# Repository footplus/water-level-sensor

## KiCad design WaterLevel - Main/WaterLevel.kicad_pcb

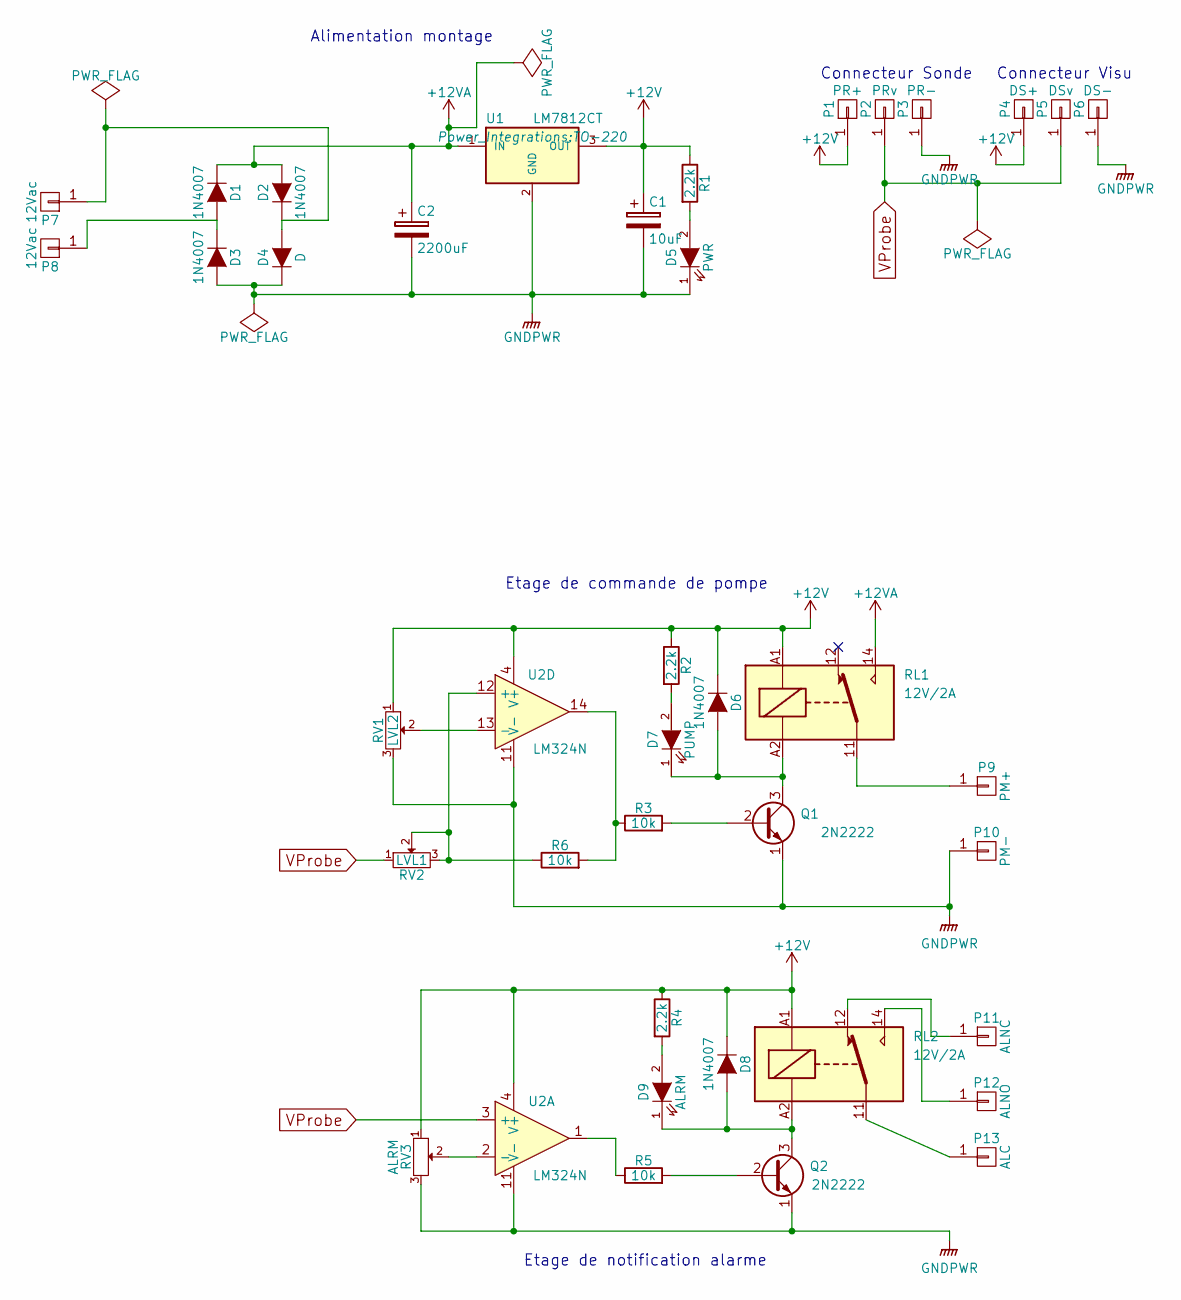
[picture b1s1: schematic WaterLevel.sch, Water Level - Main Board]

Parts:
C1: 10uF; C_Radial_D5_L11_P2.5
C2: 2200uF; C_Radial_D14_L25_P5
D1, D2, D3, D6, D8: 1N4007; Diode_DO-41_SOD81_Horizontal_RM10
D4: D; Diode_DO-41_SOD81_Horizontal_RM10
D5: PWR; LED-5MM
D7: PUMP; LED-5MM
D9: ALRM; LED-5MM
P1: PR+; Big_Square_Pad_3mm_1mmDrill
P2: PRv; Big_Square_Pad_3mm_1mmDrill
P3: PR-; Big_Square_Pad_3mm_1mmDrill
P4: DS+; Big_Square_Pad_3mm_1mmDrill
P5: DSv; Big_Square_Pad_3mm_1mmDrill
P6: DS-; Big_Square_Pad_3mm_1mmDrill
P7, P8: 12Vac; Big_Square_Pad_3mm_1mmDrill
P9: PM+; Big_Square_Pad_3mm_1mmDrill
P10: PM-; Big_Square_Pad_3mm_1mmDrill
P11: ALNC; Big_Square_Pad_3mm_1mmDrill
P12: ALNO; Big_Square_Pad_3mm_1mmDrill
P13: ALC; Big_Square_Pad_3mm_1mmDrill
Q1, Q2: 2N2222; TO-18_3Pin
R1, R2, R4: 2.2k; Resistor_Horizontal_RM7mm
R3, R5, R6: 10k; Resistor_Horizontal_RM7mm
RL1, RL2: 12V/2A; Relay_1RT_Hongfa_HF33F
RV1: LVL2; Potentiometer_Trimmer-Piher_PT10-V10_horizontal
RV2: LVL1; Potentiometer_Trimmer-Piher_PT10-V10_horizontal
RV3: ALRM; Potentiometer_Trimmer-Piher_PT10-V10_horizontal
U1: LM7812CT; TO-220
U2: LM324N; DIP-14_W7.62mm_LongPads

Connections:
+12V: C1.1, D6.1 (K), D8.1 (K), P1.1, P4.1, R1.1, R2.1, R4.1, RL1.A1, RL2.A1, RV1.1, RV3.1, U1.3 (OUT), U2.4 (V+)
+12VA: C2.1, D1.1 (K), D2.2 (A), RL1.14, U1.1 (IN)
GNDPWR: C1.2, C2.2, D3.2 (A), D4.1 (K), D5.1 (K), P3.1, P6.1, P10.1, Q1.1 (E), Q2.1 (E), RV1.3, RV3.3, U1.2 (GND), U2.11 (V-)
unnamed: D1.2 (A), D3.1 (K), P8.1
unnamed: D2.1 (K), D4.2 (A), P7.1
unnamed: D5.2 (A), R1.2
unnamed: D6.2 (A), D7.1 (K), Q1.3 (C), RL1.A2
unnamed: D7.2 (A), R2.2
unnamed: D8.2 (A), D9.1 (K), Q2.3 (C), RL2.A2
unnamed: D9.2 (A), R4.2
unnamed: P9.1, RL1.11
unnamed: P11.1, RL2.12
unnamed: P12.1, RL2.14
unnamed: P13.1, RL2.11
unnamed: Q1.2 (B), R3.2
unnamed: Q2.2 (B), R5.2
unnamed: R3.1, R6.2, U2.14
unnamed: R5.1, U2.1
unnamed: R6.1, RV2.2, RV2.3, U2.12 (+)
unnamed: RV1.2, U2.13 (-)
unnamed: RV3.2, U2.2 (-)
VProbe: P2.1, P5.1, RV2.1, U2.3 (+)

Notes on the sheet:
Alimentation montage
Etage de commande de pompe
Connecteur Sonde
Etage de notification alarme
Connecteur Visu

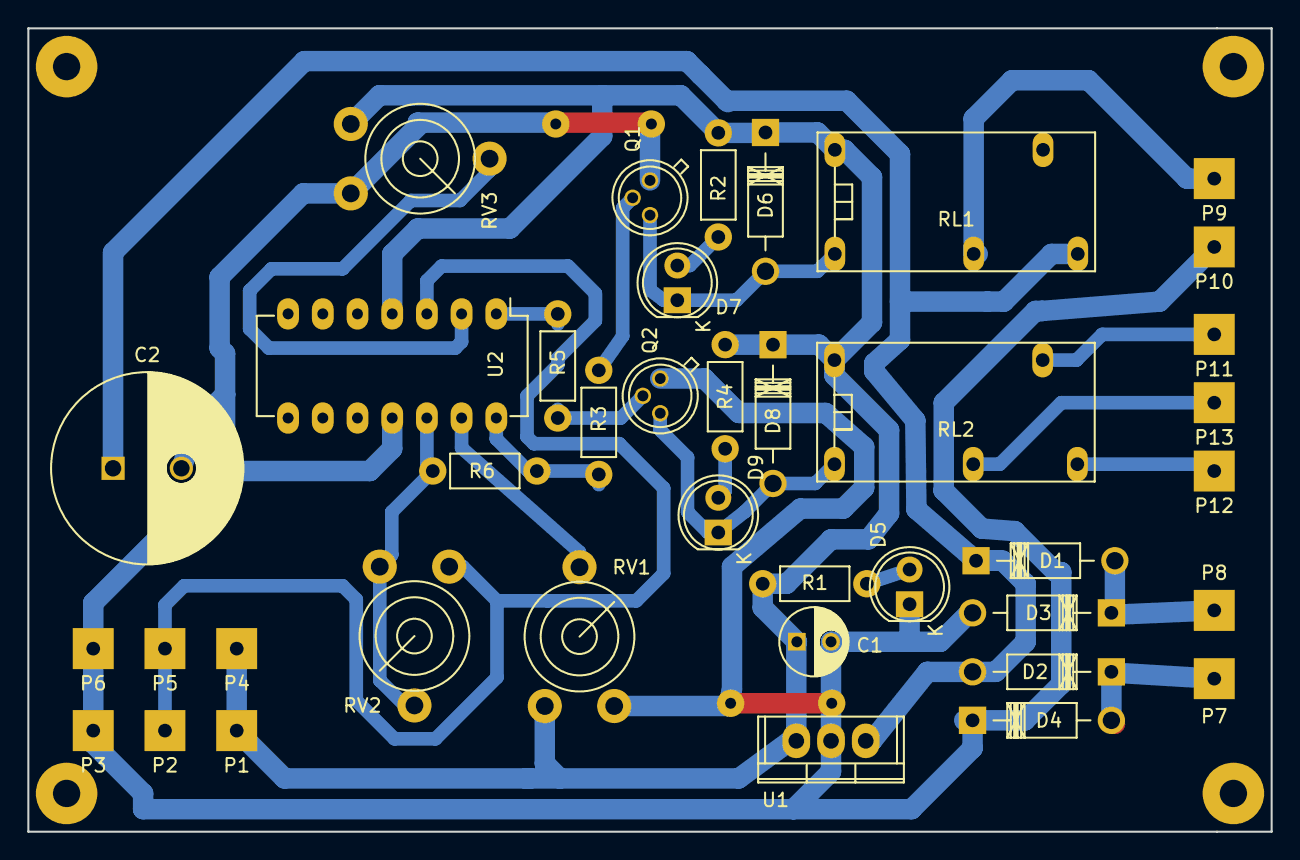
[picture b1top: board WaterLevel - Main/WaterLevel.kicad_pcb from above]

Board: 2 copper layers, 91.0 x 58.8 mm, 39 parts (0 on the bottom side), 22 nets.

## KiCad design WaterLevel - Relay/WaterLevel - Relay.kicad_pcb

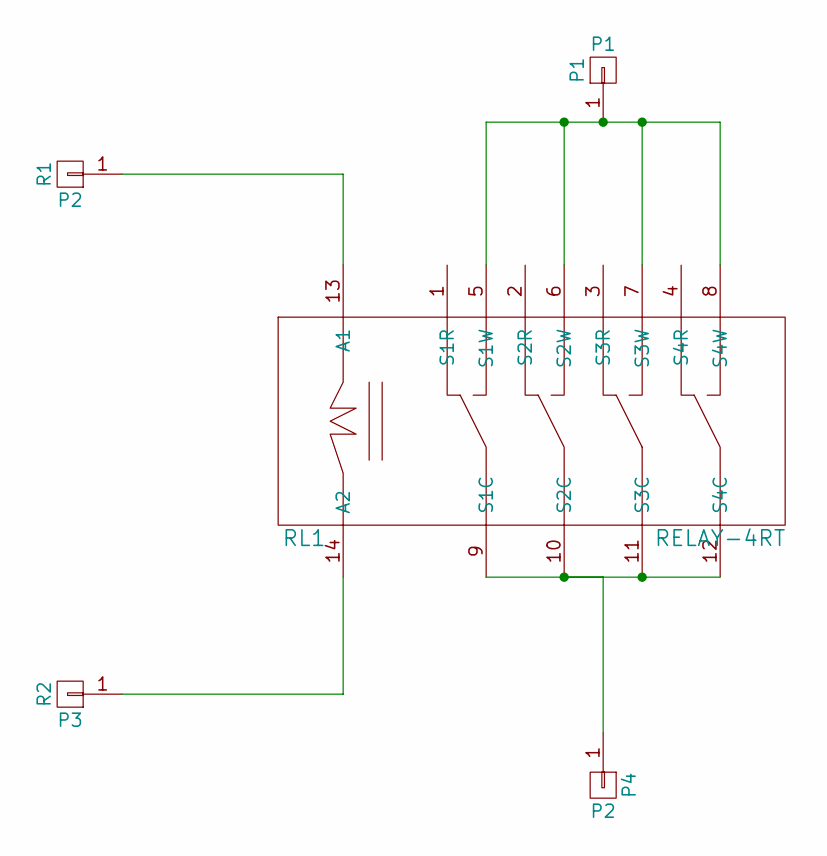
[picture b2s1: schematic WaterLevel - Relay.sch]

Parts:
P1: P1; SolderWirePad_single_2mmDrill
P2: R1; SolderWirePad_single_2mmDrill
P3: R2; SolderWirePad_single_2mmDrill
P4: P2; SolderWirePad_single_2mmDrill
RL1: RELAY-4RT; Relay_4RT_Hongfa_HF18FF

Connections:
unnamed: P1.1, RL1.5 (S1W), RL1.6 (S2W), RL1.7 (S3W), RL1.8 (S4W)
unnamed: P2.1, RL1.13 (A1)
unnamed: P3.1, RL1.14 (A2)
unnamed: P4.1, RL1.9 (S1C), RL1.10 (S2C), RL1.11 (S3C), RL1.12 (S4C)

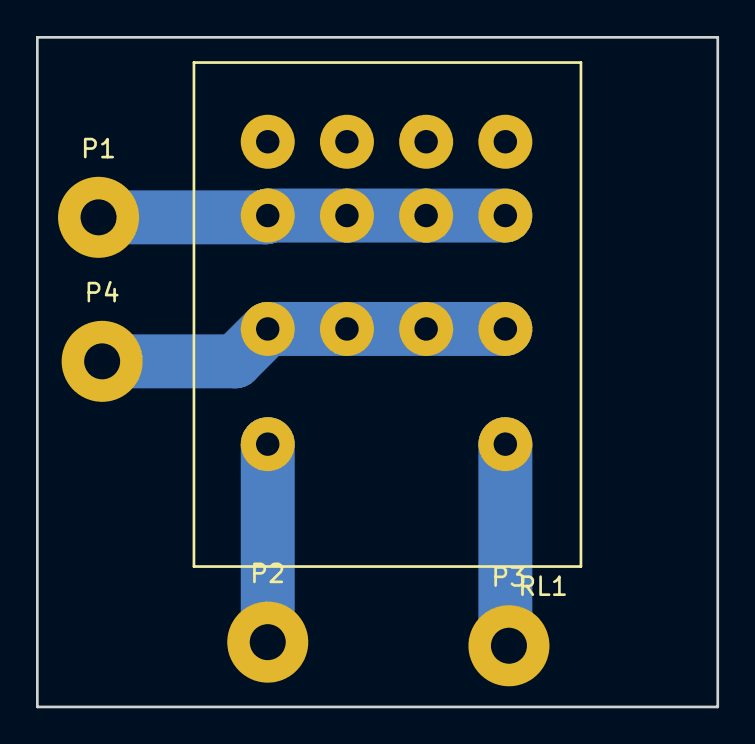
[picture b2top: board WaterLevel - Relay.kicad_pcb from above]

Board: 2 copper layers, 37.8 x 37.2 mm, 5 parts (0 on the bottom side), 4 nets.

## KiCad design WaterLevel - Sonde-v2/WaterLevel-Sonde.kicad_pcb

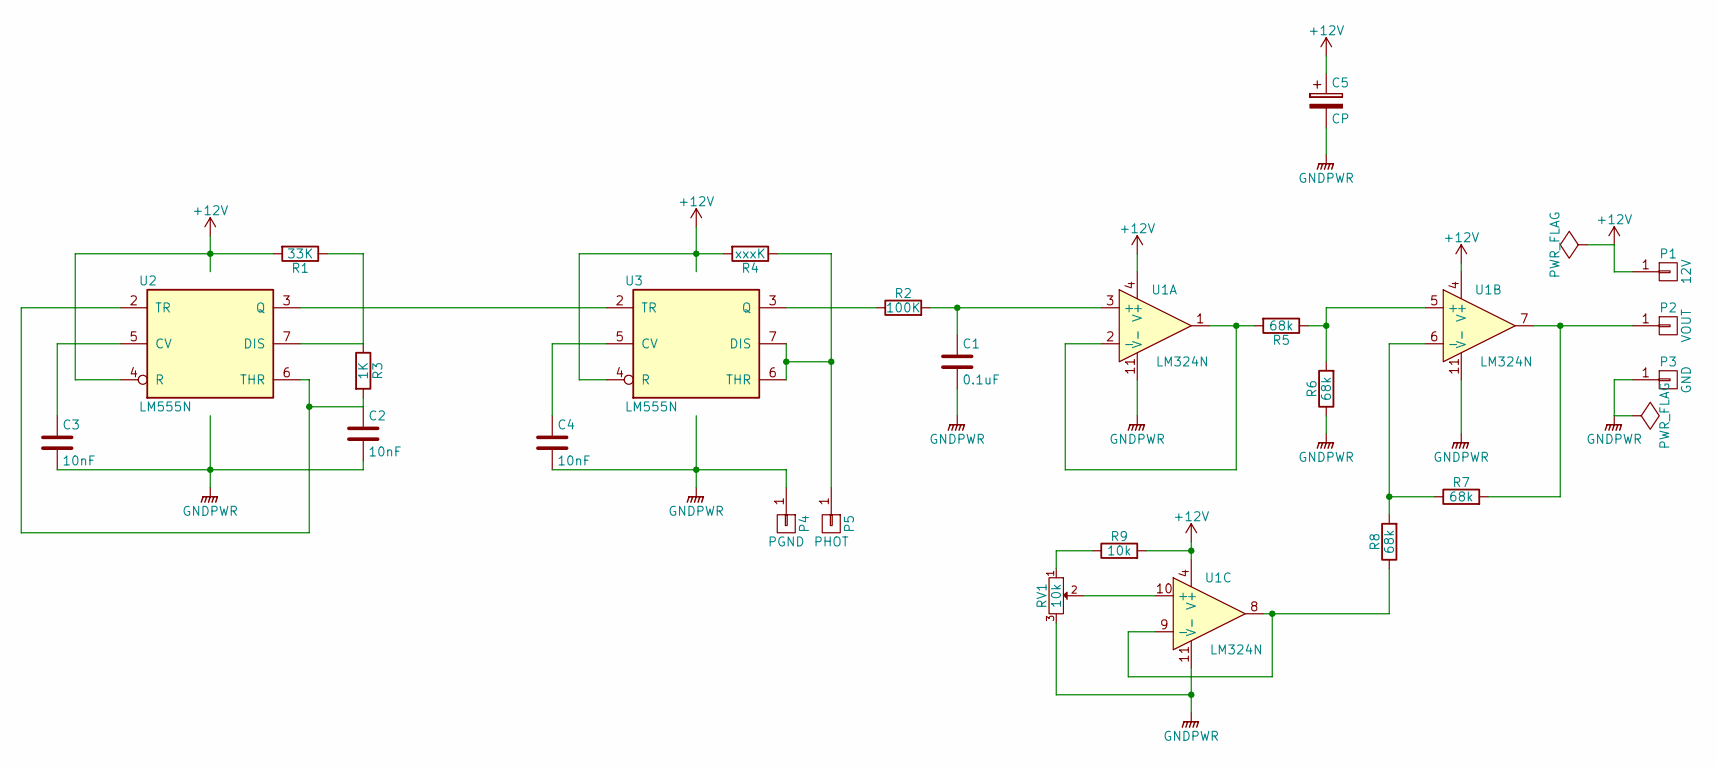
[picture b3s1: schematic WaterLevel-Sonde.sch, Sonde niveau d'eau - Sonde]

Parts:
C1: 0.1uF; C_Rect_L4_W2.5_P2.5
C2, C3: 10nF; C_Rect_L4_W2.5_P2.5
C4: 10nF; C_Rect_L7_W2.5_P5
C5: CP; C_Radial_D5_L11_P2.5
P1: 12V; Big_Square_Pad_3mm_1mmDrill
P2: VOUT; Big_Square_Pad_3mm_1mmDrill
P3: GND; Big_Square_Pad_3mm_1mmDrill
P4: PGND; Big_Square_Pad_3mm_1mmDrill
P5: PHOT; Big_Square_Pad_3mm_1mmDrill
R1: 33K; Resistor_Horizontal_RM7mm
R2: 100K; Resistor_Horizontal_RM7mm
R3: 1K; Resistor_Horizontal_RM7mm
R4: xxxK; Resistor_Horizontal_RM7mm
R5, R6, R7, R8: 68k; Resistor_Horizontal_RM7mm
R9: 10k; Resistor_Horizontal_RM7mm
RV1: 10k; Potentiometer_Spectrol-Type43
U1: LM324N; DIP-14_W7.62mm_LongPads
U2, U3: LM555N; DIP-8_W7.62mm_LongPads

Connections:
+12V: C5.1, P1.1, R1.2, R4.2, R9.2, U1.4 (V+), U2.4 (R), U2.8 (VCC), U3.4 (R), U3.8 (VCC)
GND: C1.2, C2.2, C3.2, C4.2, C5.2, P3.1, P4.1, R6.1, RV1.3, U1.11 (V-), U2.1 (GND), U3.1 (GND)
unnamed: C1.1, R2.2, U1.3 (+)
unnamed: C2.1, R3.2, U2.2 (TR), U2.6 (THR)
unnamed: C3.1, U2.5 (CV)
unnamed: C4.1, U3.5 (CV)
unnamed: P2.1, R7.2, U1.7
unnamed: P5.1, R4.1, U3.6 (THR), U3.7 (DIS)
unnamed: R1.1, R3.1, U2.7 (DIS)
unnamed: R2.1, U3.3 (Q)
unnamed: R5.1, R6.2, U1.5 (+)
unnamed: R5.2, U1.1, U1.2 (-)
unnamed: R7.1, R8.2, U1.6 (-)
unnamed: R8.1, U1.8, U1.9 (-)
unnamed: R9.1, RV1.1
unnamed: RV1.2, U1.10 (+)
unnamed: U2.3 (Q), U3.2 (TR)

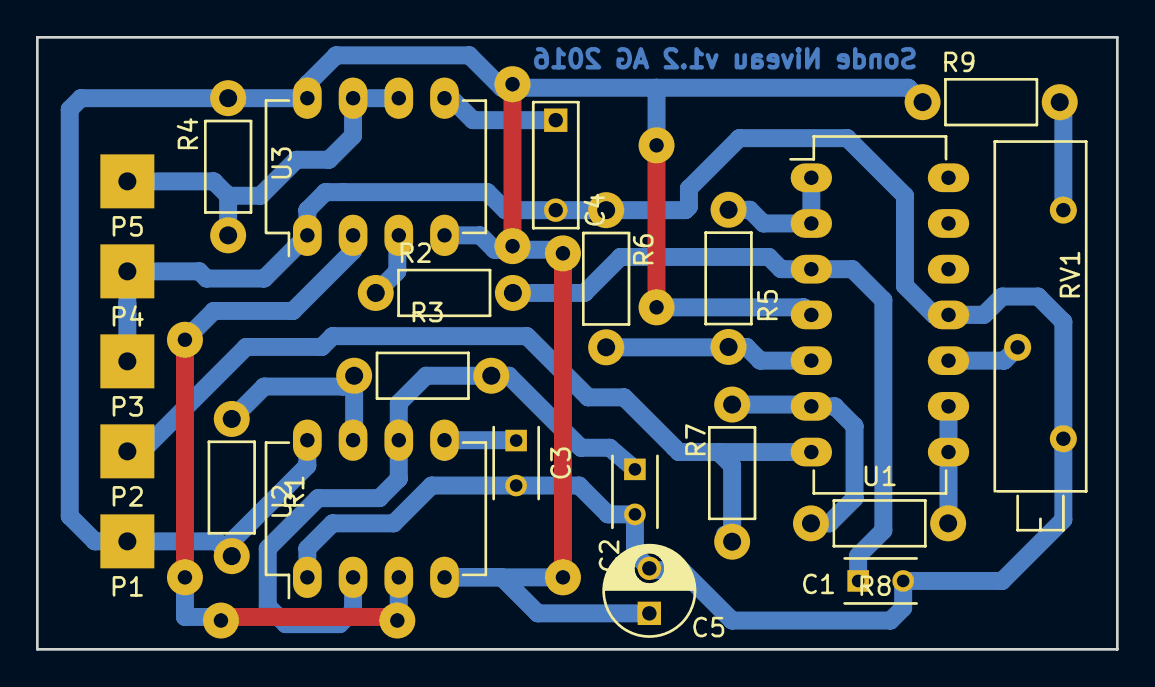
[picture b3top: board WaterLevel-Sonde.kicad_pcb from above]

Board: 2 copper layers, 60.0 x 34.0 mm, 23 parts (0 on the bottom side), 17 nets.

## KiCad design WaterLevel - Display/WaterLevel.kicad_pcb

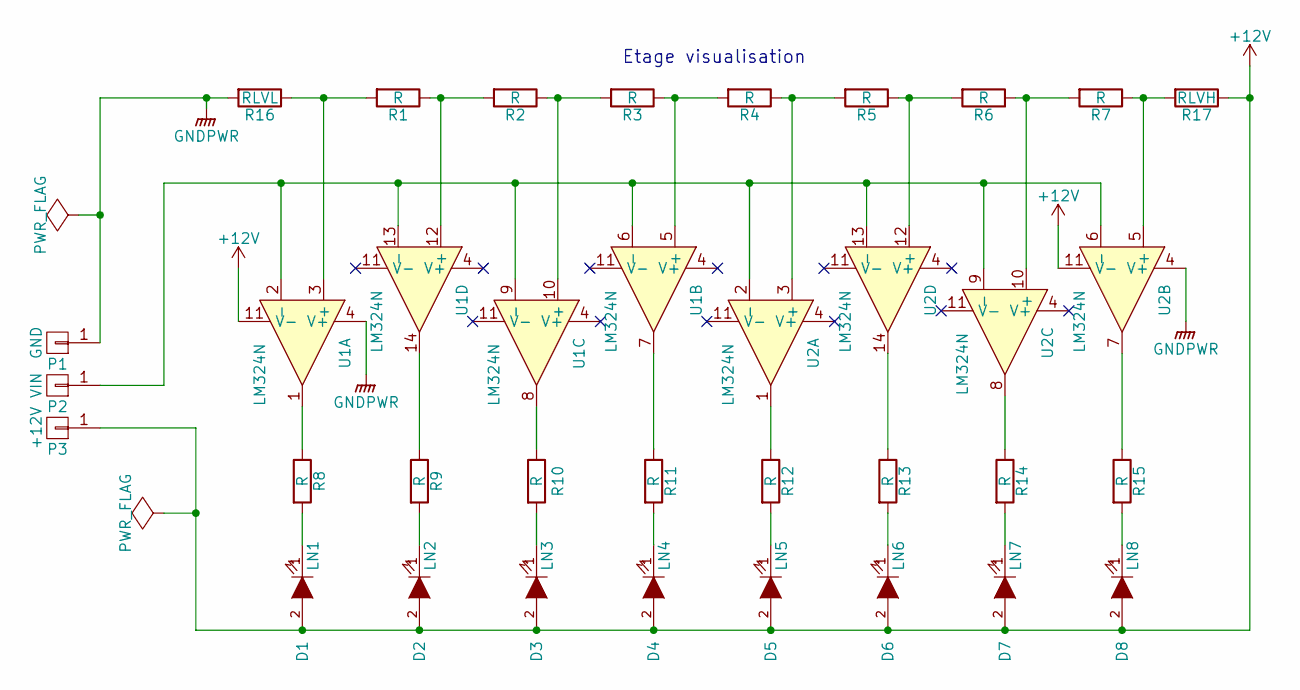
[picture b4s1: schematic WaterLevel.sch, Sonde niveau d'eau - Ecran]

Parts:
D1: LN1; LED-5MM
D2: LN2; LED-5MM
D3: LN3; LED-5MM
D4: LN4; LED-5MM
D5: LN5; LED-5MM
D6: LN6; LED-5MM
D7: LN7; LED-5MM
D8: LN8; LED-5MM
P1: GND; SolderWirePad_single_1mmDrill
P2: VIN; SolderWirePad_single_1mmDrill
P3: +12V; SolderWirePad_single_1mmDrill
R1, R2, R3, R4, R5, R6, R7, R8, R9, R10, R11, R12, R13, R14, R15: R; Resistor_Horizontal_RM7mm
R16: RLVL; Resistor_Horizontal_RM7mm
R17: RLVH; Resistor_Horizontal_RM7mm
U1, U2: LM324N; DIP-14_W7.62mm_LongPads

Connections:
+12V: D1.2 (A), D2.2 (A), D3.2 (A), D4.2 (A), D5.2 (A), D6.2 (A), D7.2 (A), D8.2 (A), P3.1, R17.1, U1.11 (V-), U2.11 (V-)
GNDPWR: P1.1, R16.2, U1.4 (V+), U2.4 (V+)
unnamed: D1.1 (K), R8.2
unnamed: D2.1 (K), R9.2
unnamed: D3.1 (K), R10.2
unnamed: D4.1 (K), R11.2
unnamed: D5.1 (K), R12.2
unnamed: D6.1 (K), R13.2
unnamed: D7.1 (K), R14.2
unnamed: D8.1 (K), R15.2
unnamed: P2.1, U1.2 (-), U1.6 (-), U1.9 (-), U1.13 (-), U2.2 (-), U2.6 (-), U2.9 (-), U2.13 (-)
unnamed: R1.1, R2.2, U1.12 (+)
unnamed: R1.2, R16.1, U1.3 (+)
unnamed: R2.1, R3.2, U1.10 (+)
unnamed: R3.1, R4.2, U1.5 (+)
unnamed: R4.1, R5.2, U2.3 (+)
unnamed: R5.1, R6.2, U2.12 (+)
unnamed: R6.1, R7.2, U2.10 (+)
unnamed: R8.1, U1.1
unnamed: R9.1, U1.14
unnamed: R10.1, U1.8
unnamed: R11.1, U1.7
unnamed: R12.1, U2.1
unnamed: R13.1, U2.14
unnamed: R14.1, U2.8
unnamed: R15.1, U2.7
unnamed: R7.1, R17.2, U2.5 (+)

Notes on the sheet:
Etage visualisation

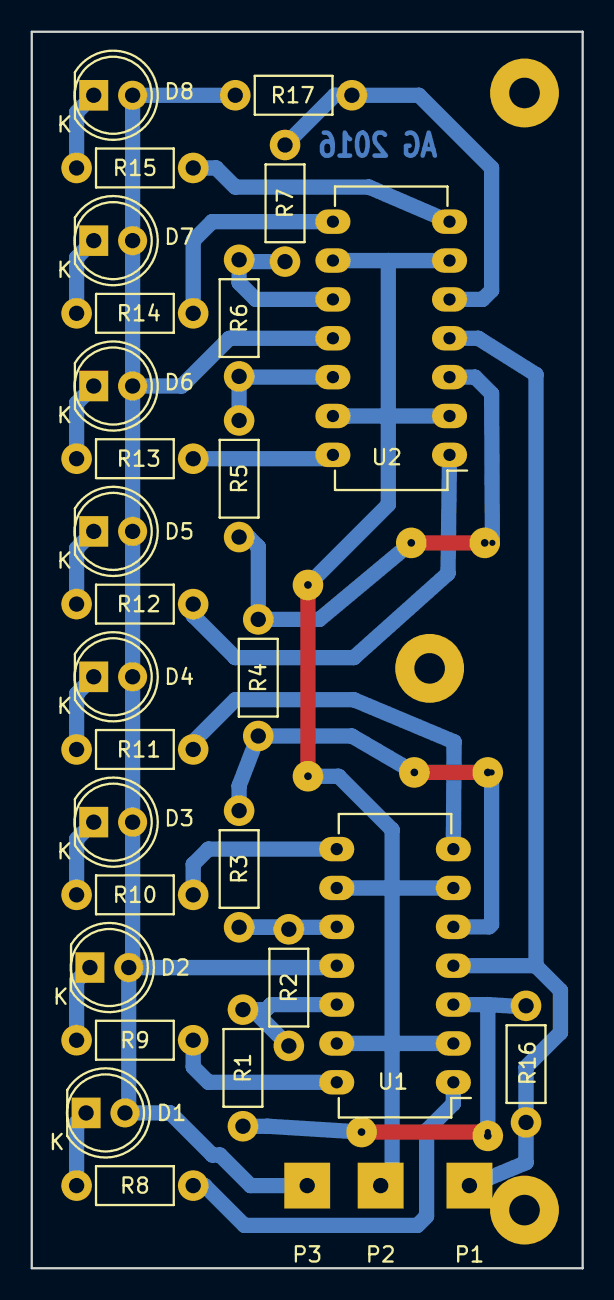
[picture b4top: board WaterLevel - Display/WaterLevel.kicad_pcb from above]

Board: 2 copper layers, 36.0 x 80.8 mm, 38 parts (0 on the bottom side), 27 nets.

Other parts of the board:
na: na; Big_Square_Pad_3mm_1mmDrill
via11, via12, via13, via21, via22, via25, via35: via; Big_Square_Pad_3mm_1mmDrill

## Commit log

2016-06-28 Init import
2016-06-28 Base PCB
2016-06-28 PCB implem
2016-06-29 Display
2016-06-29 PCB changes
2016-07-16 Fixed Sonde Before display test
2016-07-16 Final version of display
2016-07-17 Fixed a few issues with the probe, added copyright.
